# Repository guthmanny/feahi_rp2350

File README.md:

# SP-1

Soran **SP-1** 采样器与音序器：**产品语义（平台无关）** + **硬件 profile** + **参考 target**。

| 芯片（参考单板） | 职责 |
|------------------|------|
| **RP2350** + PSRAM | 音频引擎、存储、Pad/Seq/FX、USB Audio、MIDI |
| **ESP32-C6** | 8080 UI、键/灯、BLE/WiFi、IPC（可选拆分） |

音频宿主与算法见 [docs/audio-engine.md](docs/audio-engine.md)（kbuss + NuDSP）。UI 见 [docs/ui.md](docs/ui.md)（AtomTheme LVGL，与 bleach 画面分离）。前面板仿真见 [docs/panel.md](docs/panel.md)。

## 规范 vs 实现

| 层级 | 位置 | 移植时要什么 |
|------|------|----------------|
| **SP-1 操作语义** | **[spec/](spec/)** | Intent/State、样本 ref、FX 目录、IPC  envelope |
| **App / 框架** | 同级 `../feahi/` | FEAHI Port + Pad/Seq 实现契约 |
| **本板接线** | [hardware/profiles/](hardware/) | binding（Pad/LED/GPIO） |
| **参考固件** | [targets/rp2350-c6/](targets/rp2350-c6/) | Pico SDK + ESP-IDF 示例 |

**SP-1 的行为**（按下 Pad 触发什么、灯怎么表示状态、工程/样本如何引用）由 **spec** 定义；**NAND 还是 NOR、3729 还是 PWM** 由你的 target 决定。

> 规范版本：`spec/` **0.1.0-draft**。参考硬件/固件不代表规范的一部分。

嵌入式框架：[FEAHI](../feahi/) · 音频迁移参考：[feahi_pico](../feahi_pico)

## 仓库布局

```
├── spec/                 # ★ 产品契约（平台无关）
├── docs/                 # 架构说明（含 audio-engine / ui / panel）
├── hardware/profiles/    # sp-1 单板 · b-c6 模板
├── targets/rp2350-c6/    # 参考 target
├── ui/                   # SP-1 屏幕库（PC 仿真与 C6 共用）
├── ui_sim/               # PC：LVGL + SDL（LCD）；shell/ 为机壳键钮
└── panel/                # 前面板事件（pad/encoder/LED），无 GUI
```

## 设计约束（参考单板 SP-1）

1. Engine 握样本存储；UI 不直接擦写 Flash（见 [spec/voice-and-sample.md](spec/voice-and-sample.md)）  
2. USB Audio 在 Engine 侧（当前 profile）  
3. IPC 仅传 Intent/State（见 [spec/ipc.md](spec/ipc.md)）  
4. 键/灯语义见 [spec/intents.md](spec/intents.md)  

细节与 GPIO 草案：[docs/hardware.md](docs/hardware.md)

## 依赖（参考 target）

- Pico SDK ≥ 2.2.0 · ESP-IDF ≥ 5.2  
- `../feahi/`、`../qdsp/`

## 构建

```powershell
cd targets/rp2350-c6/rp2350_sound
# cmake / build.ps1

cd ..\c6_host
# idf.py build
```

PC 屏幕 + 机壳仿真：

```bash
cmake -S ui_sim -B ui_sim/build
cmake --build ui_sim/build
./ui_sim/build/sp1_ui_sim
```

## KiCad

| Profile | 工程 |
|---------|------|
| 单板 | [hardware/profiles/sp-1/kicad/sp-1.kicad_pro](hardware/profiles/sp-1/kicad/sp-1.kicad_pro) |
| CBI-40 模板 | [sp1_cbi40_periph](hardware/profiles/b-c6/kicad/sp1_cbi40_periph/sp1_cbi40_periph.kicad_pro) |

## 文档

- [spec 索引](spec/README.md) · [架构](docs/architecture.md) · [硬件](docs/hardware.md)
- [音频引擎分层（kbuss + NuDSP）](docs/audio-engine.md)
- [UI 分层（AtomTheme LVGL，与 bleach 分离）](docs/ui.md)
- [前面板仿真（按键 / 旋钮 / LED）](docs/panel.md)
- [Pad/Seq（FEAHI）](../feahi/docs/)

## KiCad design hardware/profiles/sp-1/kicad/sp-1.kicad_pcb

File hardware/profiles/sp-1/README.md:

# SP-1 单板 Profile

量产 **4L 单板** KiCad 工程：RP2350、ESP32-C6、MS1808/MS4344、8080 屏、键灯、接口与电源。

## KiCad

打开：**File → Open Project** →  
[hardware/profiles/sp-1/kicad/sp-1.kicad_pro](kicad/sp-1.kicad_pro)

子页：`core.kicad_sch`、`c6.kicad_sch`、`audio.kicad_sch`、`power.kicad_sch` 等。

## 原理图辅助文档

网表与 UI 分配见 [../b-c6/schematic/](../b-c6/schematic/)（`sp1_*.csv` / `sp1_*.md` 与单板共用）。

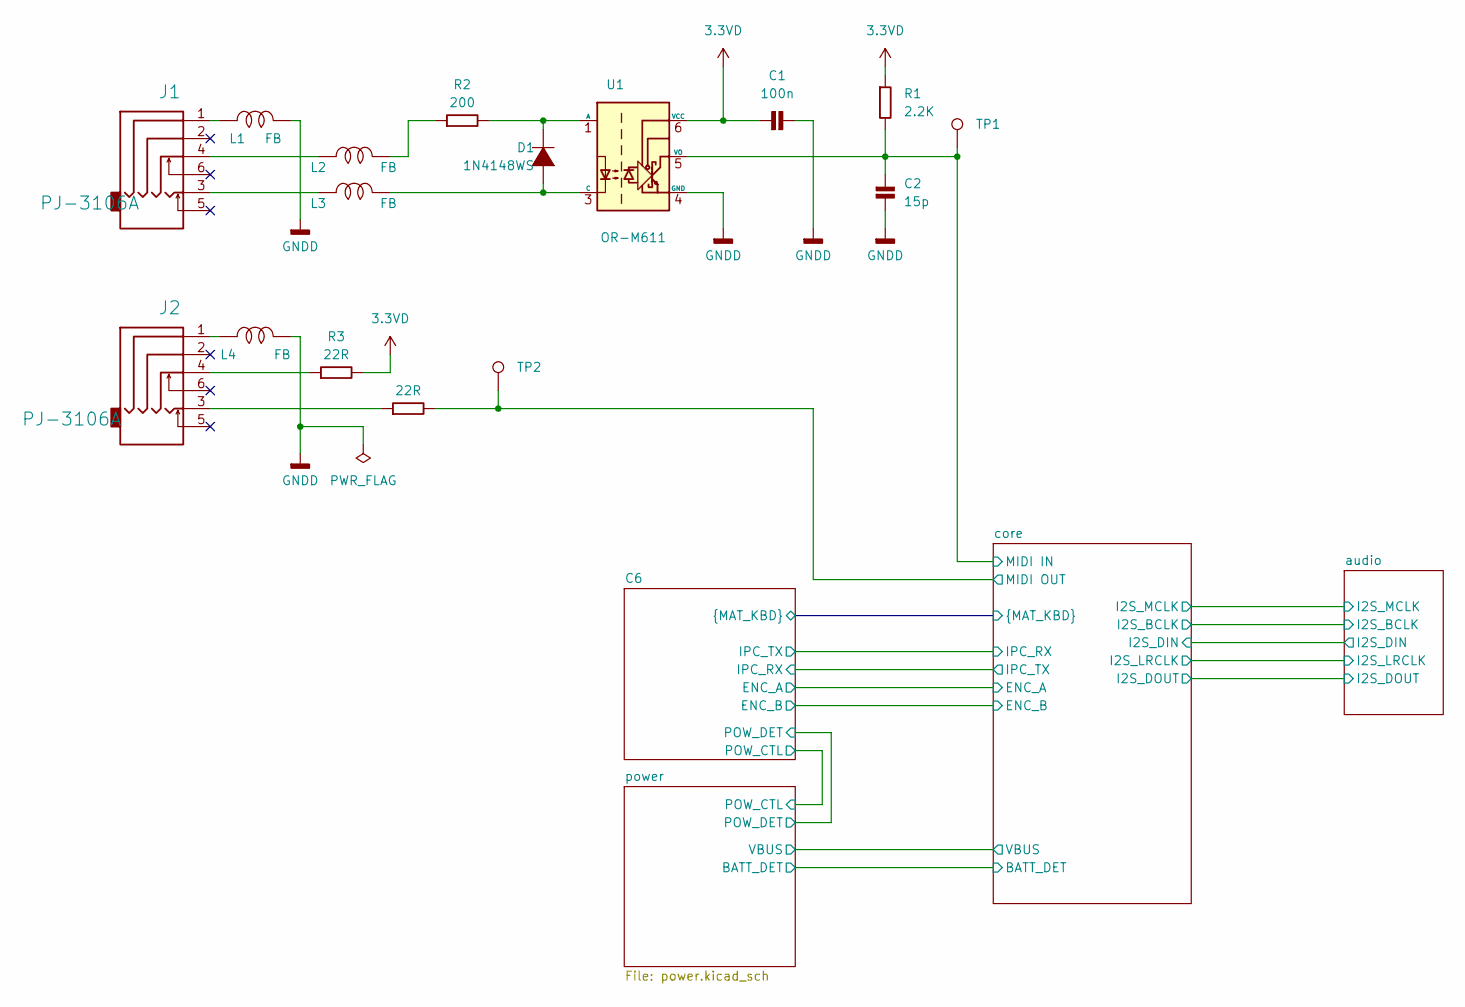
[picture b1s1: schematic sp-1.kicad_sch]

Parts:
C1: 100n; C_0402_1005Metric_Pad0.74x0.62mm_HandSolder
C2: 15p; C_0402_1005Metric_Pad0.74x0.62mm_HandSolder
D1: 1N4148WS; SOD-323
J1, J2: PJ-3106A; PJ3106A
L1, L2, L3, L4: FB; L_0603_1608Metric
R1: 2.2K; R_0402_1005Metric_Pad0.72x0.64mm_HandSolder
R2: 200; R_0402_1005Metric_Pad0.72x0.64mm_HandSolder
R3, R4: 22R; R_0402_1005Metric_Pad0.72x0.64mm_HandSolder
TP1: TP; TEST POINT
TP2: TP; TestPoint_Keystone_5000-5004_Miniature
U1: OR-M611; SO-5-6_4.55x3.7mm_P1.27mm; Part Number OR-M611-TP-G-(HB)

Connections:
3.3VD: C1.1, R1.1, R3.2, U1.6 (VCC); also elsewhere on the board
/core/MIDI IN: C2.1, R1.2, TP1.1 (1_1), U1.5 (VO); also elsewhere on the board
/core/MIDI OUT: R4.2, TP2.1 (1_1); also elsewhere on the board
GNDD: C1.2, C2.2, L1.2, L4.2, U1.4 (GND); also elsewhere on the board
unnamed: D1.1 (A), L3.2, U1.3 (C)
unnamed: D1.2 (K), R2.2, U1.1 (A)
unnamed: J1.1, L1.1
unnamed: J1.3, L3.1
unnamed: J1.4, L2.1
unnamed: J2.1, L4.1
unnamed: J2.3, R4.1
unnamed: J2.4, R3.1
unnamed: L2.2, R2.1

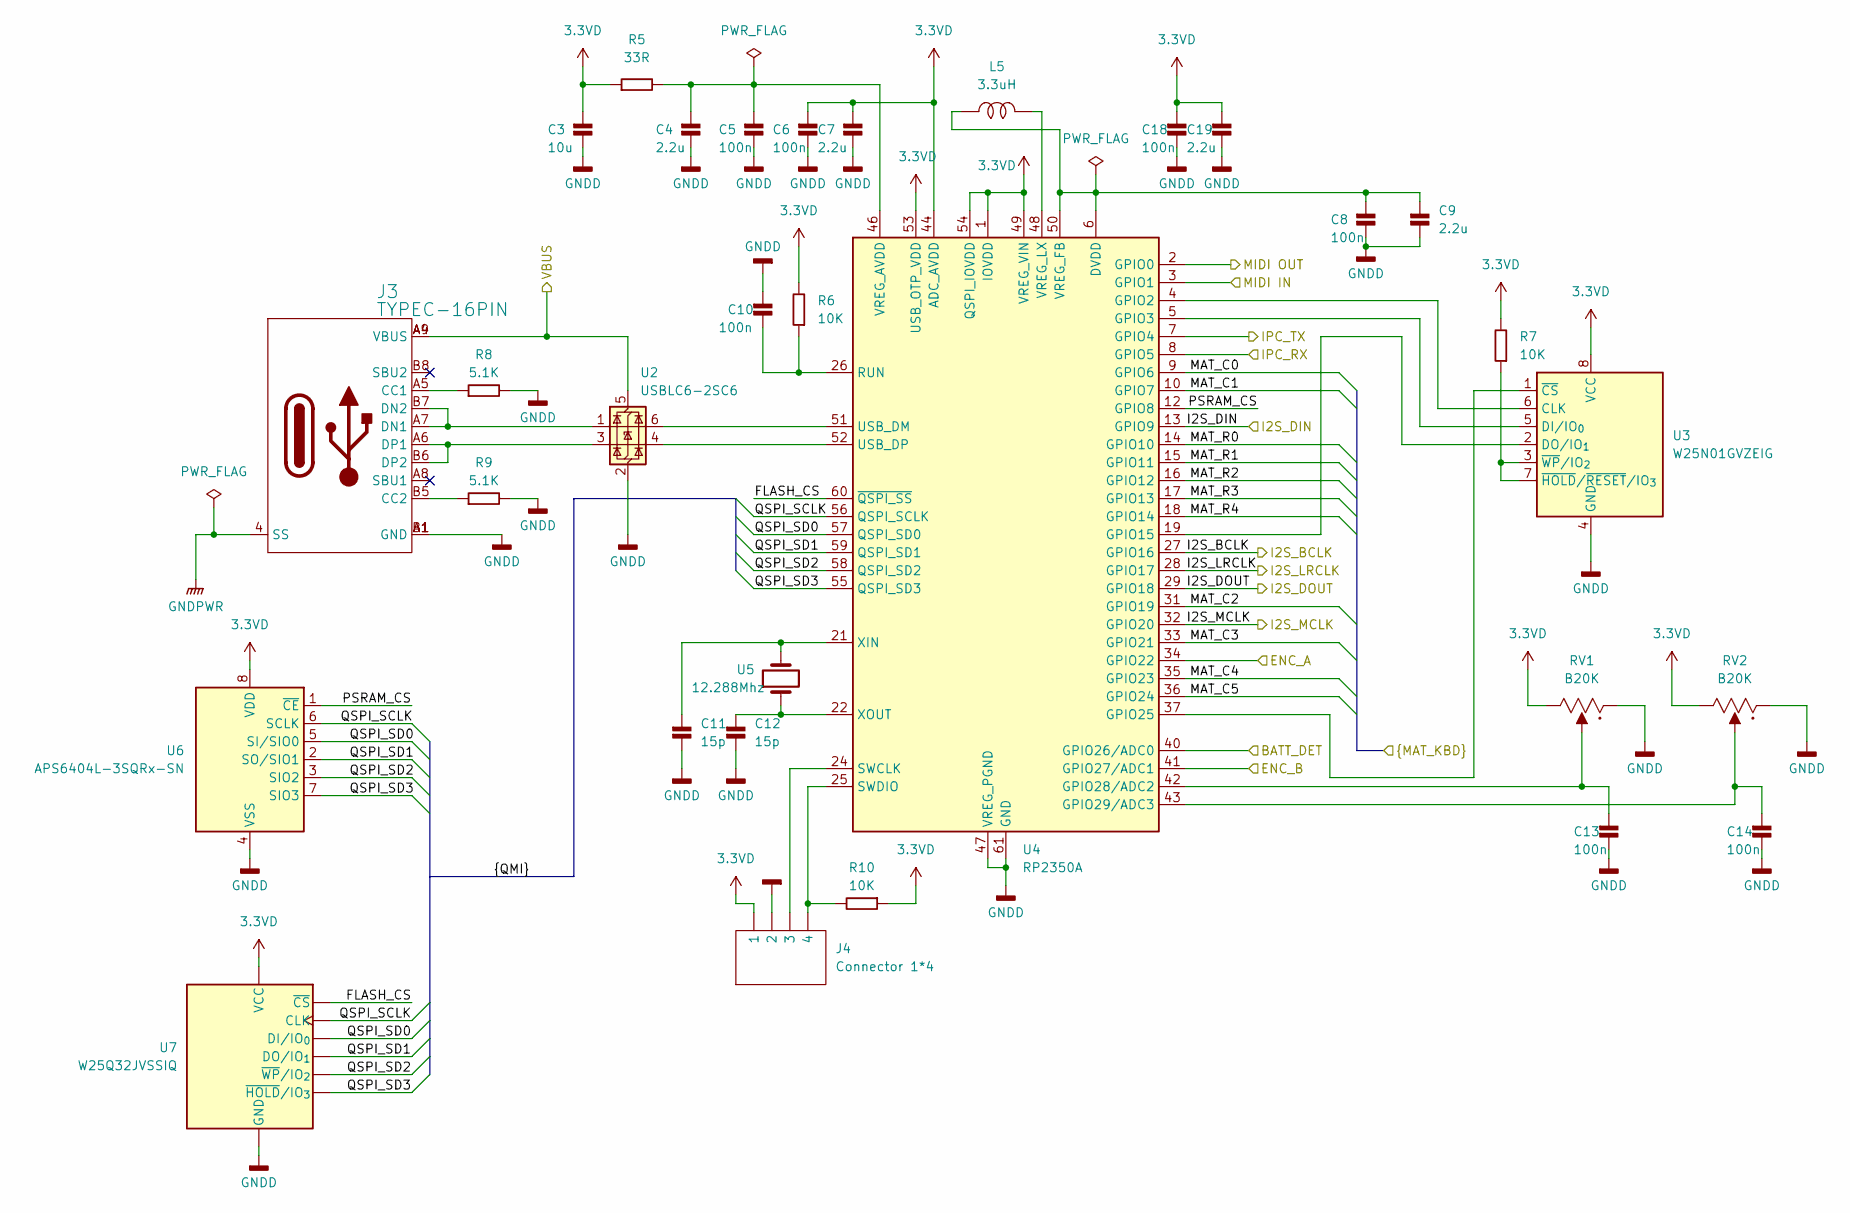
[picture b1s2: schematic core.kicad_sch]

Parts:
C3: 10u; C_0603_1608Metric_Pad1.08x0.95mm_HandSolder
C4, C7, C9, C19: 2.2u; C_0402_1005Metric_Pad0.74x0.62mm_HandSolder
C5, C6, C8, C10, C13, C14, C18: 100n; C_0402_1005Metric_Pad0.74x0.62mm_HandSolder
C11, C12: 15p; C_0402_1005Metric_Pad0.74x0.62mm_HandSolder
J3: TYPEC-16PIN; TYPEC-PIN12
J4: Connector 1*4; CN2.54P4
L5: 3.3uH; L_Cenker_CKCS201610
R5: 33R; R_0603_1608Metric_Pad0.98x0.95mm_HandSolder
R6, R7, R10: 10K; R_0402_1005Metric_Pad0.72x0.64mm_HandSolder
R8, R9: 5.1K; R_0402_1005Metric_Pad0.72x0.64mm_HandSolder
RV1, RV2: B20K; 9MM V POT_7.5mm
U2: USBLC6-2SC6; SOT-23-6
U3: W25N01GVZEIG; WSON-8-1EP_8x6mm_P1.27mm_EP3.4x4.3mm
U4: RP2350A; QFN-60-1EP_7x7mm_P0.4mm_EP3.4x3.4mm
U5: 12.288Mhz; Crystal_SMD_3225-4Pin_3.2x2.5mm
U6: APS6404L-3SQRx-SN; SOIC-8_3.9x4.9mm_P1.27mm
U7: W25Q32JVSSIQ; SOIC-8_5.3x5.3mm_P1.27mm; Part Number W25Q32JVSSIQ

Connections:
3.3VD: C3.1, C6.1, C7.1, C18.1, C19.1, J4.1, R5.1, R6.2, R7.2, R10.1, RV1.3, RV2.3, U3.8 (VCC), U4.1 (IOVDD), U4.11 (IOVDD), U4.20 (IOVDD), U4.30 (IOVDD), U4.38 (IOVDD), U4.44 (ADC_AVDD), U4.45 (IOVDD), U4.49 (VREG_VIN), U4.53 (USB_OTP_VDD), U4.54 (QSPI_IOVDD), U6.8 (VDD), U7.8 (VCC); also elsewhere on the board
/C6/ENC_A: U4.34 (GPIO22)
/C6/ENC_B: U4.41 (GPIO27/ADC1)
/C6/IPC_RX: U4.7 (GPIO4); also elsewhere on the board
/C6/IPC_TX: U4.8 (GPIO5); also elsewhere on the board
/C6/MAT_C0: U4.9 (GPIO6); also elsewhere on the board
/C6/MAT_C1: U4.10 (GPIO7); also elsewhere on the board
/C6/MAT_C2: U4.31 (GPIO19); also elsewhere on the board
/C6/MAT_C3: U4.33 (GPIO21); also elsewhere on the board
/C6/MAT_C4: U4.35 (GPIO23); also elsewhere on the board
/C6/MAT_C5: U4.36 (GPIO24); also elsewhere on the board
/C6/MAT_R0: U4.14 (GPIO10); also elsewhere on the board
/C6/MAT_R1: U4.15 (GPIO11); also elsewhere on the board
/C6/MAT_R2: U4.16 (GPIO12); also elsewhere on the board
/C6/MAT_R3: U4.17 (GPIO13); also elsewhere on the board
/C6/MAT_R4: U4.18 (GPIO14); also elsewhere on the board
/audio/I2S_BCLK: U4.27 (GPIO16); also elsewhere on the board
/audio/I2S_DIN: U4.13 (GPIO9); also elsewhere on the board
/audio/I2S_DOUT: U4.29 (GPIO18); also elsewhere on the board
/audio/I2S_LRCLK: U4.28 (GPIO17); also elsewhere on the board
/audio/I2S_MCLK: U4.32 (GPIO20); also elsewhere on the board
/core/BATT_DET: U4.40 (GPIO26/ADC0); also elsewhere on the board
/core/FLASH_CS: U4.60 (~QSPI_SS), U7.1 (~CS)
/core/MIDI IN: U4.3 (GPIO1); also elsewhere on the board
/core/MIDI OUT: U4.2 (GPIO0); also elsewhere on the board
/core/PSRAM_CS: U4.12 (GPIO8), U6.1 (~CE)
/core/QSPI_SCLK: U4.56 (QSPI_SCLK), U6.6 (SCLK), U7.6 (CLK)
/core/QSPI_SD0: U4.57 (QSPI_SD0), U6.5 (SI/SIO0), U7.5 (DI/IO_{0})
/core/QSPI_SD1: U4.59 (QSPI_SD1), U6.2 (SO/SIO1), U7.2 (DO/IO_{1})
/core/QSPI_SD2: U4.58 (QSPI_SD2), U6.3 (SIO2), U7.3 (~WP/IO_{2})
/core/QSPI_SD3: U4.55 (QSPI_SD3), U6.7 (SIO3), U7.7 (~HOLD/IO_{3})
/core/VBUS: J3.A4 (VBUS), J3.A9 (VBUS), J3.B4 (VBUS), J3.B9 (VBUS), U2.5 (VBUS); also elsewhere on the board
GNDD: C3.2, C4.2, C5.2, C6.2, C7.2, C8.2, C9.2, C10.1, C11.2, C12.2, C13.2, C14.2, C18.2, C19.2, J3.A1 (GND), J3.A12 (GND), J3.B1 (GND), J3.B12 (GND), J4.2, R8.2, R9.2, RV1.1, RV2.1, U2.2 (GND), U3.4 (GND), U4.47 (VREG_PGND), U4.61 (GND), U6.4 (VSS), U7.4 (GND); also elsewhere on the board
GNDPWR: J3.1 (SS), J3.2 (SS), J3.3 (SS), J3.4 (SS); also elsewhere on the board
unnamed: J3.A5 (CC1), R8.1
unnamed: J3.B5 (CC2), R9.1
unnamed: J3.A7 (DN1), J3.B7 (DN2), U2.1 (I/O1)
unnamed: J3.A6 (DP1), J3.B6 (DP2), U2.3 (I/O2)
unnamed: U3.6 (CLK), U4.4 (GPIO2)
unnamed: U3.5 (DI/IO_{0}), U4.5 (GPIO3)
unnamed: U3.2 (DO/IO_{1}), U4.19 (GPIO15)
unnamed: U3.1 (~CS), U4.37 (GPIO25)
unnamed: R7.1, U3.3 (~WP/IO_{2}), U3.7 (~HOLD/~RESET/IO_{3})
unnamed: C13.1, RV1.2, U4.42 (GPIO28/ADC2)
unnamed: C14.1, RV2.2, U4.43 (GPIO29/ADC3)
unnamed: C10.2, R6.1, U4.26 (RUN)
unnamed: J4.3, U4.24 (SWCLK)
unnamed: J4.4, R10.2, U4.25 (SWDIO)
unnamed: U2.6 (I/O1), U4.51 (USB_DM)
unnamed: U2.4 (I/O2), U4.52 (USB_DP)
unnamed: C4.1, C5.1, R5.2, U4.46 (VREG_AVDD)
unnamed: C8.1, C9.1, L5.1, U4.6 (DVDD), U4.23 (DVDD), U4.39 (DVDD), U4.50 (VREG_FB)
unnamed: L5.2, U4.48 (VREG_LX)
unnamed: C11.1, U4.21 (XIN), U5.2
unnamed: C12.1, U4.22 (XOUT), U5.1

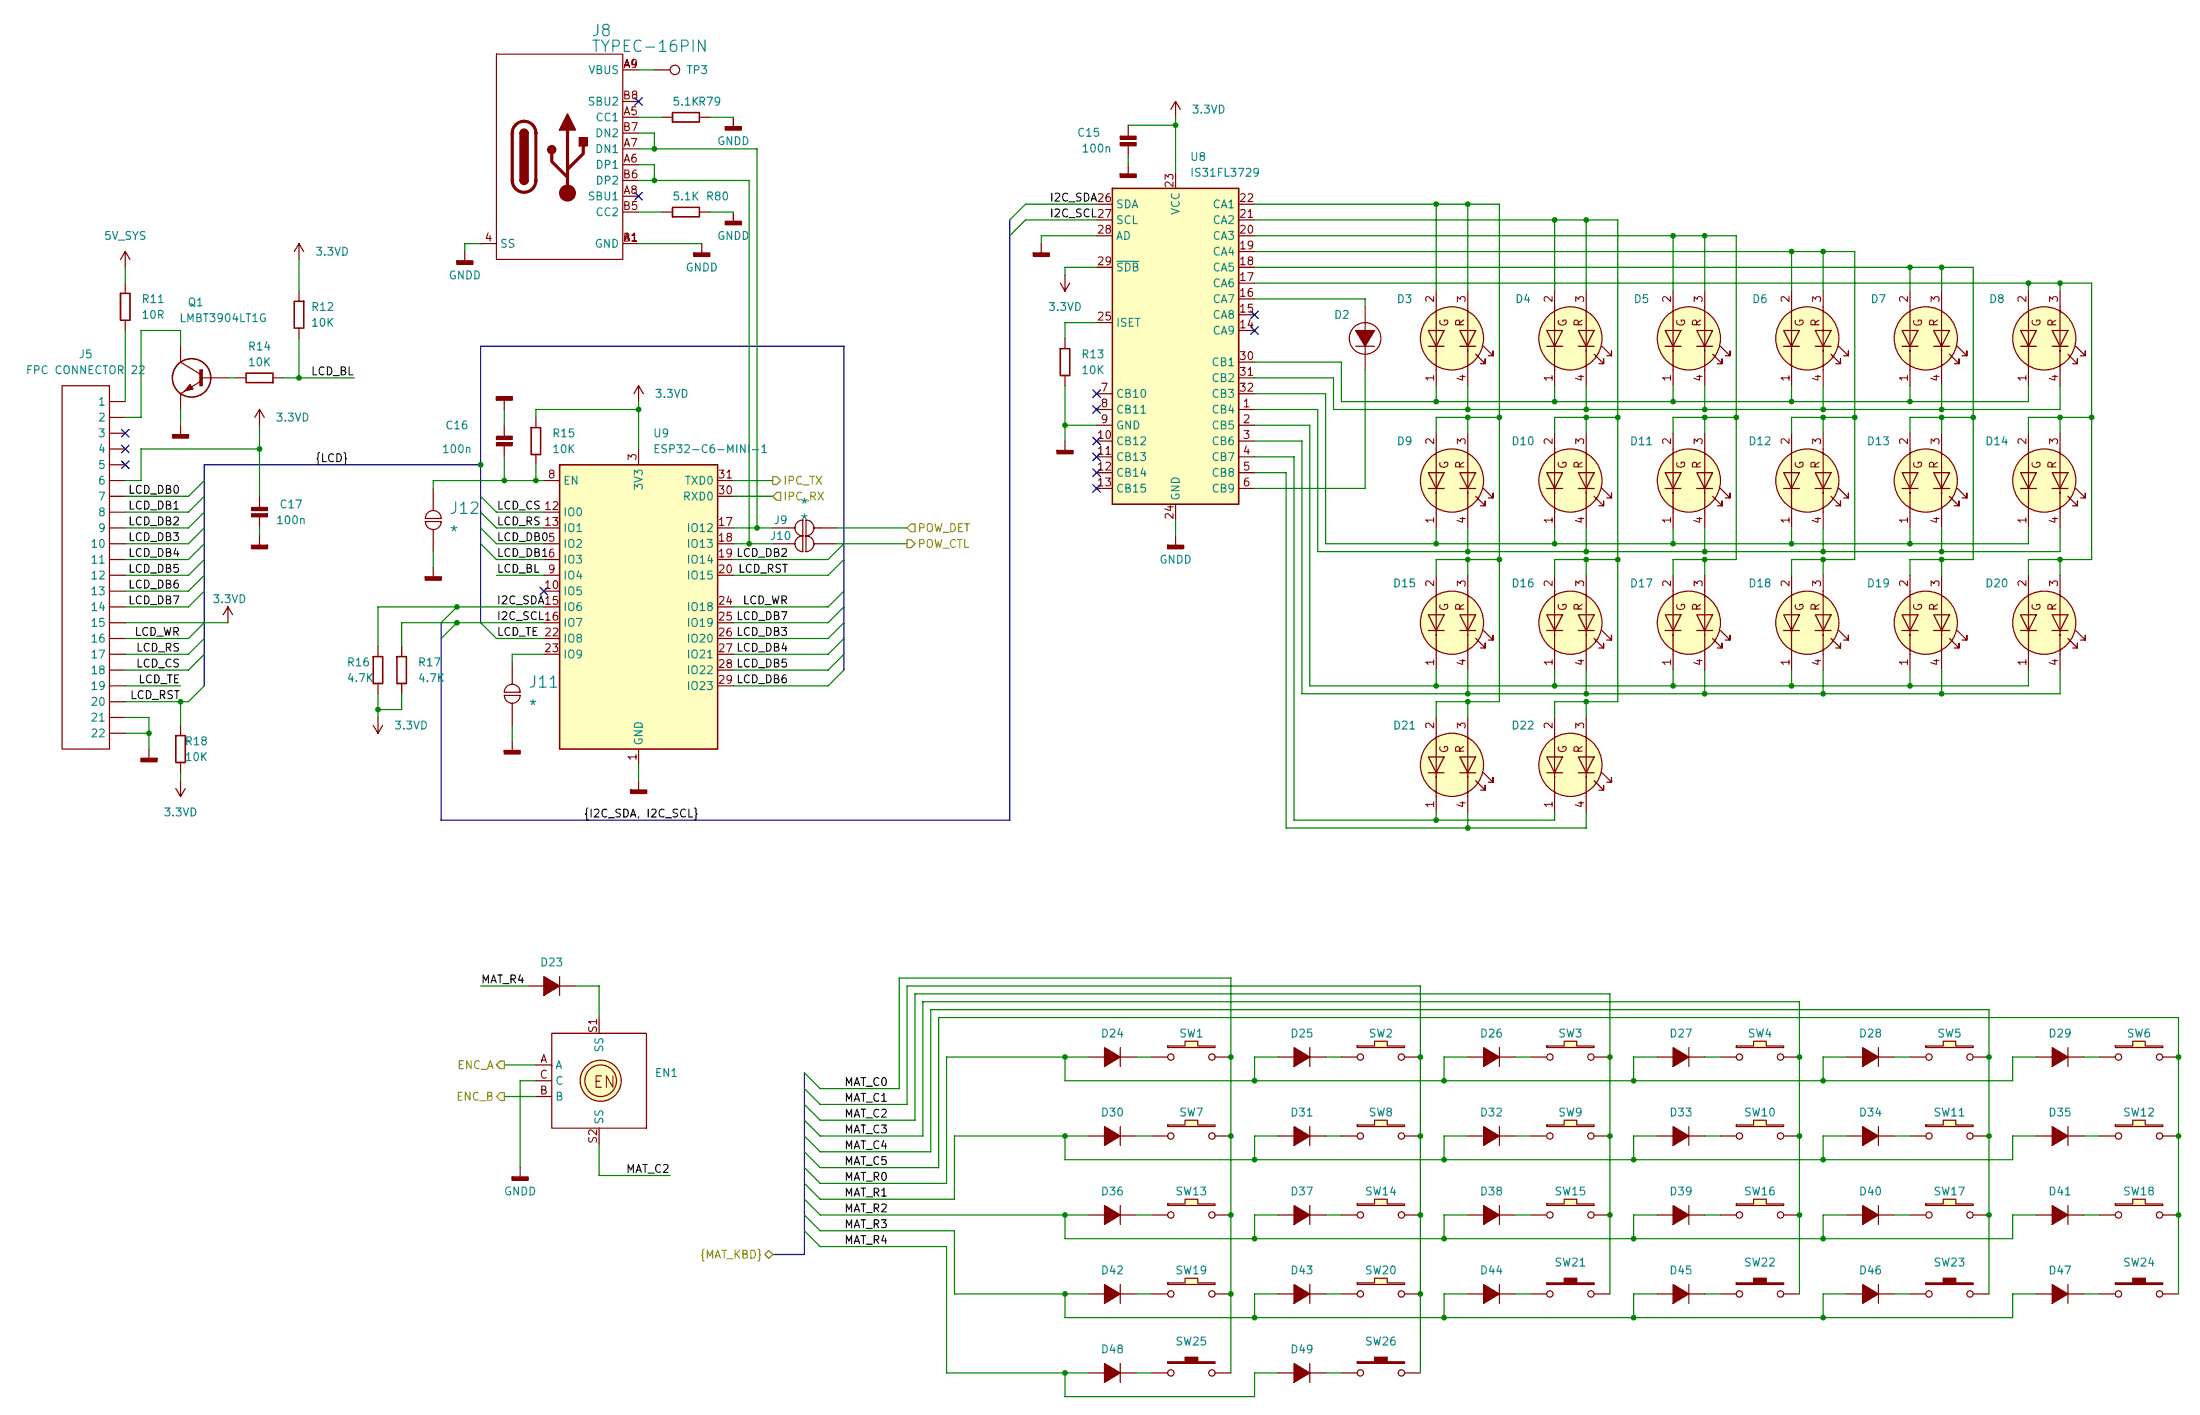
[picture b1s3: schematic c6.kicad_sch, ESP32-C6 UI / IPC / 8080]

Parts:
C15, C16, C17: 100n; C_0402_1005Metric_Pad0.74x0.62mm_HandSolder
D2: 0402 LED; LED0402
D3, D4, D5, D6, D7, D8, D9, D10, D11, D12, D13, D14, D15, D16, D17, D18, D19, D20, D21, D22: LTST-C235KGKRKT; LED_LiteOn_LTST-C235KGKRKT
D23, D24, D25, D26, D27, D28, D29, D30, D31, D32, D33, D34, D35, D36, D37, D38, D39, D40, D41, D42, D43, D44, D45, D46, D47, D48, D49: 1N4148WS; SOD-323
EN1: TEMPO; 11mm Encoder
J5: FPC CONNECTOR 22; 22PIN_FPCZ
J8: TYPEC-16PIN; TYPEC-PIN12
J9, J10, J11, J12: *; BYPASS
Q1: LMBT3904LT1G; SOT-23
R11: 10R; R_0402_1005Metric_Pad0.72x0.64mm_HandSolder
R12, R13, R14, R15, R18: 10K; R_0402_1005Metric_Pad0.72x0.64mm_HandSolder
R16, R17: 4.7K; R_0402_1005Metric_Pad0.72x0.64mm_HandSolder
R79, R80: 5.1K; R_0402_1005Metric_Pad0.72x0.64mm_HandSolder
SW1, SW2, SW3, SW4, SW5, SW6, SW7, SW8, SW9, SW10, SW11, SW12, SW13, SW14, SW15, SW16, SW17, SW18, SW19, SW20: CPG1353; SW_Kailh_Choc_V2
SW21, SW22, SW23, SW24, SW25, SW26: SMD TACT SWITCH; SW-T-SMT - 1
TP3: TP; TEST POINT
U8: IS31FL3729; QFN-32
U9: ESP32-C6-MINI-1

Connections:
3.3VD: C15.1, C17.1, J5.6, J5.15, R12.1, R15.1, R16.2, R17.2, R18.2, U8.23 (VCC), U8.29 (~SDB), U9.3 (3V3); also elsewhere on the board
5V_SYS: R11.1; also elsewhere on the board
/C6/I2C_SCL: R17.1, U8.27 (SCL), U9.16 (IO7)
/C6/I2C_SDA: R16.1, U8.26 (SDA), U9.15 (IO6)
/C6/IPC_RX: U9.30 (RXD0); also elsewhere on the board
/C6/IPC_TX: U9.31 (TXD0); also elsewhere on the board
/C6/LCD_BL: R12.2, R14.1, U9.9 (IO4)
/C6/LCD_CS: J5.18, U9.12 (IO0)
/C6/LCD_DB0: J5.7, U9.5 (IO2)
/C6/LCD_DB1: J5.8, U9.6 (IO3)
/C6/LCD_DB2: J5.9, U9.19 (IO14)
/C6/LCD_DB3: J5.10, U9.26 (IO20)
/C6/LCD_DB4: J5.11, U9.27 (IO21)
/C6/LCD_DB5: J5.12, U9.28 (IO22)
/C6/LCD_DB6: J5.13, U9.29 (IO23)
/C6/LCD_DB7: J5.14, U9.25 (IO19)
/C6/LCD_RS: J5.17, U9.13 (IO1)
/C6/LCD_RST: J5.20, R18.1, U9.20 (IO15)
/C6/LCD_TE: J5.19, U9.22 (IO8)
/C6/LCD_WR: J5.16, U9.24 (IO18)
/C6/MAT_C0: SW1.2, SW7.2, SW13.2, SW19.2, SW25.2; also elsewhere on the board
/C6/MAT_C1: SW2.2, SW8.2, SW14.2, SW20.2, SW26.2; also elsewhere on the board
/C6/MAT_C2: EN1.S2 (SS), SW3.2, SW9.2, SW15.2, SW21.2; also elsewhere on the board
/C6/MAT_C3: SW4.2, SW10.2, SW16.2, SW22.2; also elsewhere on the board
/C6/MAT_C4: SW5.2, SW11.2, SW17.2, SW23.2; also elsewhere on the board
/C6/MAT_C5: SW6.2, SW12.2, SW18.2, SW24.2; also elsewhere on the board
/C6/MAT_R0: D24.1 (A), D25.1 (A), D26.1 (A), D27.1 (A), D28.1 (A), D29.1 (A); also elsewhere on the board
/C6/MAT_R1: D30.1 (A), D31.1 (A), D32.1 (A), D33.1 (A), D34.1 (A), D35.1 (A); also elsewhere on the board
/C6/MAT_R2: D36.1 (A), D37.1 (A), D38.1 (A), D39.1 (A), D40.1 (A), D41.1 (A); also elsewhere on the board
/C6/MAT_R3: D42.1 (A), D43.1 (A), D44.1 (A), D45.1 (A), D46.1 (A), D47.1 (A); also elsewhere on the board
/C6/MAT_R4: D23.1 (A), D48.1 (A), D49.1 (A); also elsewhere on the board
/C6/POW_CTL: J10.2; also elsewhere on the board
/C6/POW_DET: J9.2; also elsewhere on the board
GNDD: C15.2, C16.1, C17.2, EN1.C, J5.21, J5.22, J8.1 (SS), J8.2 (SS), J8.3 (SS), J8.4 (SS), J8.A1 (GND), J8.A12 (GND), J8.B1 (GND), J8.B12 (GND), J11.1, J12.1, Q1.2 (E), R13.2, R79.2, R80.2, U8.9 (GND), U8.24 (GND), U8.28 (AD), U8.33 (GNDD), U9.1 (GND), U9.2 (GND), U9.11 (GND), U9.14 (GND), U9.36 (GND), U9.37 (GND), U9.38 (GND), U9.39 (GND), U9.40 (GND), U9.41 (GND), U9.42 (GND), U9.43 (GND), U9.44 (GND), U9.45 (GND), U9.46 (GND), U9.47 (GND), U9.48 (GND), U9.49 (GND), U9.50 (GND), U9.51 (GND), U9.52 (GND), U9.53 (GND); also elsewhere on the board
unnamed: D2.K (1), U8.6 (CB9)
unnamed: D2.A (2), U8.16 (CA7)
unnamed: D3.4 (K1), D4.4 (K1), D5.4 (K1), D6.4 (K1), D7.4 (K1), D8.4 (K1), U8.31 (CB2)
unnamed: D3.1 (K2), D4.1 (K2), D5.1 (K2), D6.1 (K2), D7.1 (K2), D8.1 (K2), U8.30 (CB1)
unnamed: D4.2 (A2), D4.3 (A1), D10.2 (A2), D10.3 (A1), D16.2 (A2), D16.3 (A1), D22.2 (A2), D22.3 (A1), U8.21 (CA2)
unnamed: D9.4 (K1), D10.4 (K1), D11.4 (K1), D12.4 (K1), D13.4 (K1), D14.4 (K1), U8.1 (CB4)
unnamed: D9.1 (K2), D10.1 (K2), D11.1 (K2), D12.1 (K2), D13.1 (K2), D14.1 (K2), U8.32 (CB3)
unnamed: D5.2 (A2), D5.3 (A1), D11.2 (A2), D11.3 (A1), D17.2 (A2), D17.3 (A1), U8.20 (CA3)
unnamed: D6.2 (A2), D6.3 (A1), D12.2 (A2), D12.3 (A1), D18.2 (A2), D18.3 (A1), U8.19 (CA4)
unnamed: D7.2 (A2), D7.3 (A1), D13.2 (A2), D13.3 (A1), D19.2 (A2), D19.3 (A1), U8.18 (CA5)
unnamed: D8.2 (A2), D8.3 (A1), D14.2 (A2), D14.3 (A1), D20.2 (A2), D20.3 (A1), U8.17 (CA6)
unnamed: D3.2 (A2), D3.3 (A1), D9.2 (A2), D9.3 (A1), D15.2 (A2), D15.3 (A1), D21.2 (A2), D21.3 (A1), U8.22 (CA1)
unnamed: D15.4 (K1), D16.4 (K1), D17.4 (K1), D18.4 (K1), D19.4 (K1), D20.4 (K1), U8.3 (CB6)
unnamed: D15.1 (K2), D16.1 (K2), D17.1 (K2), D18.1 (K2), D19.1 (K2), D20.1 (K2), U8.2 (CB5)
unnamed: D21.4 (K1), D22.4 (K1), U8.5 (CB8)
unnamed: D21.1 (K2), D22.1 (K2), U8.4 (CB7)
unnamed: D23.2 (K), EN1.S1 (SS)
unnamed: D24.2 (K), SW1.1
unnamed: D25.2 (K), SW2.1
unnamed: D26.2 (K), SW3.1
unnamed: D27.2 (K), SW4.1
unnamed: D28.2 (K), SW5.1
unnamed: D29.2 (K), SW6.1
unnamed: D30.2 (K), SW7.1
unnamed: D31.2 (K), SW8.1
unnamed: D32.2 (K), SW9.1
unnamed: D33.2 (K), SW10.1
unnamed: D34.2 (K), SW11.1
unnamed: D35.2 (K), SW12.1
unnamed: D36.2 (K), SW13.1
unnamed: D37.2 (K), SW14.1
unnamed: D38.2 (K), SW15.1
unnamed: D39.2 (K), SW16.1
unnamed: D40.2 (K), SW17.1
unnamed: D41.2 (K), SW18.1
unnamed: D42.2 (K), SW19.1
unnamed: D43.2 (K), SW20.1
unnamed: D44.2 (K), SW21.1
unnamed: D45.2 (K), SW22.1
unnamed: D46.2 (K), SW23.1
unnamed: D47.2 (K), SW24.1
unnamed: D48.2 (K), SW25.1
unnamed: D49.2 (K), SW26.1
unnamed: J5.1, R11.2
unnamed: J8.A5 (CC1), R79.1
unnamed: J8.B5 (CC2), R80.1
unnamed: J8.A7 (DN1), J8.B7 (DN2), J9.1, U9.17 (IO12)
unnamed: J8.A6 (DP1), J8.B6 (DP2), J10.1, U9.18 (IO13)
unnamed: J8.A4 (VBUS), J8.A9 (VBUS), J8.B4 (VBUS), J8.B9 (VBUS), TP3.1 (1_1)
unnamed: Q1.1 (B), R14.2
unnamed: J5.2, Q1.3 (C)
unnamed: R13.1, U8.25 (ISET)
unnamed: C16.2, J12.2, R15.2, U9.8 (EN)
unnamed: J11.2, U9.23 (IO9)

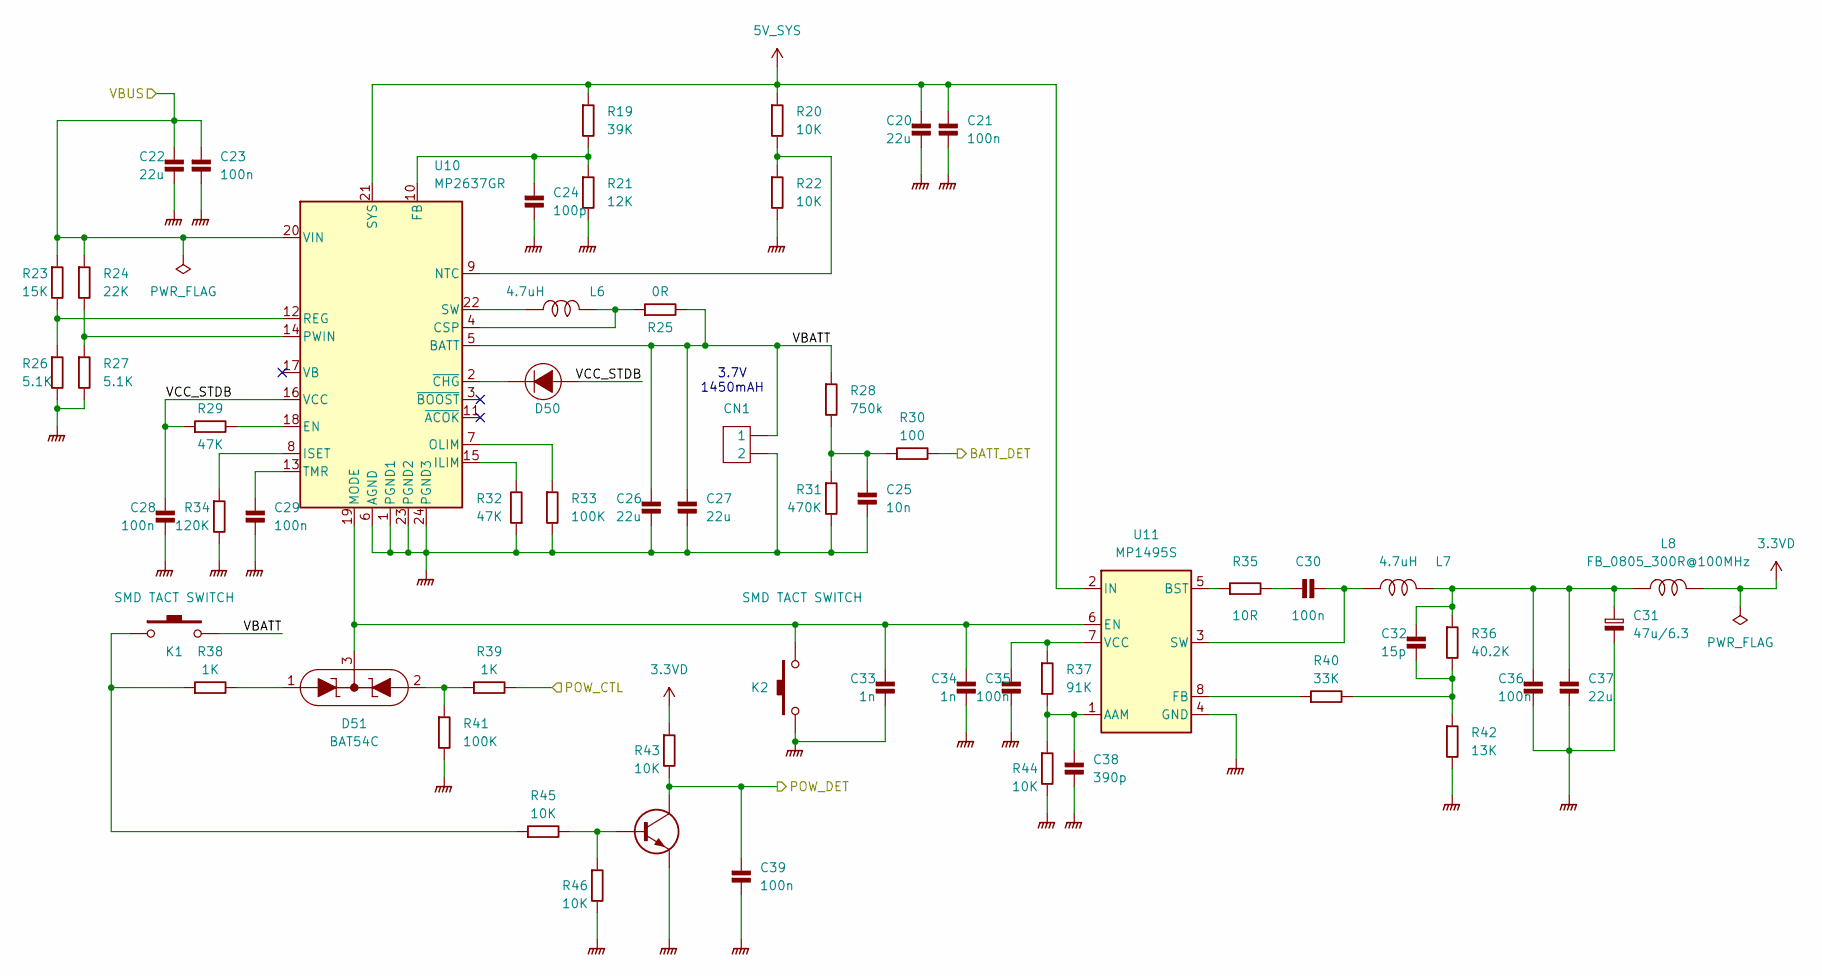
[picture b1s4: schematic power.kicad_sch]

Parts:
C20, C22, C26, C27, C37: 22u; C_0603_1608Metric_Pad1.08x0.95mm_HandSolder
C21, C23, C28, C29, C30, C35, C36, C39: 100n; C_0402_1005Metric_Pad0.74x0.62mm_HandSolder
C24: 100p; C_0402_1005Metric_Pad0.74x0.62mm_HandSolder
C25: 10n; C_0402_1005Metric_Pad0.74x0.62mm_HandSolder
C31: 47u/6.3; CP_Elec_4x5.4
C32: 15p; C_0402_1005Metric_Pad0.74x0.62mm_HandSolder
C33, C34: 1n; C_0402_1005Metric_Pad0.74x0.62mm_HandSolder
C38: 390p; C_0402_1005Metric_Pad0.74x0.62mm_HandSolder
CN1: Connector 1*2_2.0; 2PIN - 2.0
D50: 0402 LED; LED0402
D51: BAT54C; SOT-23-3
K1, K2: SMD TACT SWITCH; SW-T-SMT
L6, L7: 4.7uH; L_Sunlord_SWPA4020S
L8: FB_0805_300R@100MHz; R_0805_2012Metric_Pad1.20x1.40mm_HandSolder
Q2: LMBT3904LT1G; SOT-23
R19: 39K; R_0402_1005Metric_Pad0.72x0.64mm_HandSolder
R20, R22, R43, R44, R45, R46: 10K; R_0402_1005Metric_Pad0.72x0.64mm_HandSolder
R21: 12K; R_0402_1005Metric_Pad0.72x0.64mm_HandSolder
R23: 15K; R_0402_1005Metric_Pad0.72x0.64mm_HandSolder
R24: 22K; R_0402_1005Metric_Pad0.72x0.64mm_HandSolder
R25: 0R; R_1206_3216Metric_Pad1.30x1.75mm_HandSolder
R26, R27: 5.1K; R_0402_1005Metric_Pad0.72x0.64mm_HandSolder
R28: 750k; R_0603_1608Metric_Pad0.98x0.95mm_HandSolder
R29, R32: 47K; R_0402_1005Metric_Pad0.72x0.64mm_HandSolder
R30: 100; R_0402_1005Metric_Pad0.72x0.64mm_HandSolder
R31: 470K; R_0402_1005Metric_Pad0.72x0.64mm_HandSolder
R33, R41: 100K; R_0402_1005Metric_Pad0.72x0.64mm_HandSolder
R34: 120K; R_0402_1005Metric_Pad0.72x0.64mm_HandSolder
R35: 10R; R_0402_1005Metric_Pad0.72x0.64mm_HandSolder
R36: 40.2K; R_0603_1608Metric_Pad0.98x0.95mm_HandSolder
R37: 91K; R_0402_1005Metric_Pad0.72x0.64mm_HandSolder
R38, R39: 1K; R_0402_1005Metric_Pad0.72x0.64mm_HandSolder
R40: 33K; R_0402_1005Metric_Pad0.72x0.64mm_HandSolder
R42: 13K; R_0402_1005Metric_Pad0.72x0.64mm_HandSolder
U10: MP2637GR; QFN-24 (4mm×4mm)
U11: MP1495S; TSOT23-8

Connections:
3.3VD: L8.2, R43.1; also elsewhere on the board
5V_SYS: C20.1, C21.1, R19.1, R20.1, U10.21 (SYS), U11.2 (IN); also elsewhere on the board
/C6/POW_CTL: R39.2; also elsewhere on the board
/C6/POW_DET: C39.1, Q2.3 (C), R43.2; also elsewhere on the board
/core/BATT_DET: R30.2; also elsewhere on the board
/core/VBUS: C22.1, C23.1, R23.1, R24.1, U10.20 (VIN); also elsewhere on the board
/power/VBATT: C26.1, C27.1, CN1.1, K1.2, R25.2, R28.1, U10.5 (BATT)
/power/VCC_STDB: C28.1, D50.A (2), R29.1, U10.16 (VCC)
GNDPWR: C20.2, C21.2, C22.2, C23.2, C24.2, C25.2, C26.2, C27.2, C28.2, C29.2, C31.2, C33.2, C34.2, C35.2, C36.2, C37.2, C38.2, C39.2, CN1.2, K2.1, Q2.2 (E), R21.2, R22.2, R26.2, R27.2, R31.2, R32.1, R33.2, R34.2, R41.2, R42.2, R44.2, R46.2, U10.1 (PGND1), U10.6 (AGND), U10.23 (PGND2), U10.24 (PGND3), U11.4 (GND); also elsewhere on the board
unnamed: C25.1, R28.2, R30.1, R31.1
unnamed: C30.1, R35.2
unnamed: C31.1, C32.1, C36.1, C37.1, L7.2, L8.1, R36.1
unnamed: C32.2, R36.2, R40.2, R42.1
unnamed: D50.K (1), U10.2 (~CHG)
unnamed: D51.1 (A), R38.2
unnamed: D51.2 (A), R39.1, R41.1
unnamed: C33.1, C34.1, D51.3 (K), K2.2, U10.19 (MODE), U11.6 (EN)
unnamed: K1.1, R38.1, R45.1
unnamed: Q2.1 (B), R45.2, R46.1
unnamed: L6.2, R25.1, U10.4 (CSP)
unnamed: R29.2, U10.18 (EN)
unnamed: C24.1, R19.2, R21.1, U10.10 (FB)
unnamed: R32.2, U10.15 (ILIM)
unnamed: R34.1, U10.8 (ISET)
unnamed: R20.2, R22.1, U10.9 (NTC)
unnamed: R33.1, U10.7 (OLIM)
unnamed: R24.2, R27.1, U10.14 (PWIN)
unnamed: R23.2, R26.1, U10.12 (REG)
unnamed: L6.1, U10.22 (SW)
unnamed: C29.1, U10.13 (TMR)
unnamed: C38.1, R37.2, R44.1, U11.1 (AAM)
unnamed: R35.1, U11.5 (BST)
unnamed: R40.1, U11.8 (FB)
unnamed: C30.2, L7.1, U11.3 (SW)
unnamed: C35.1, R37.1, U11.7 (VCC)

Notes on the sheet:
3.7V 1450mAH
